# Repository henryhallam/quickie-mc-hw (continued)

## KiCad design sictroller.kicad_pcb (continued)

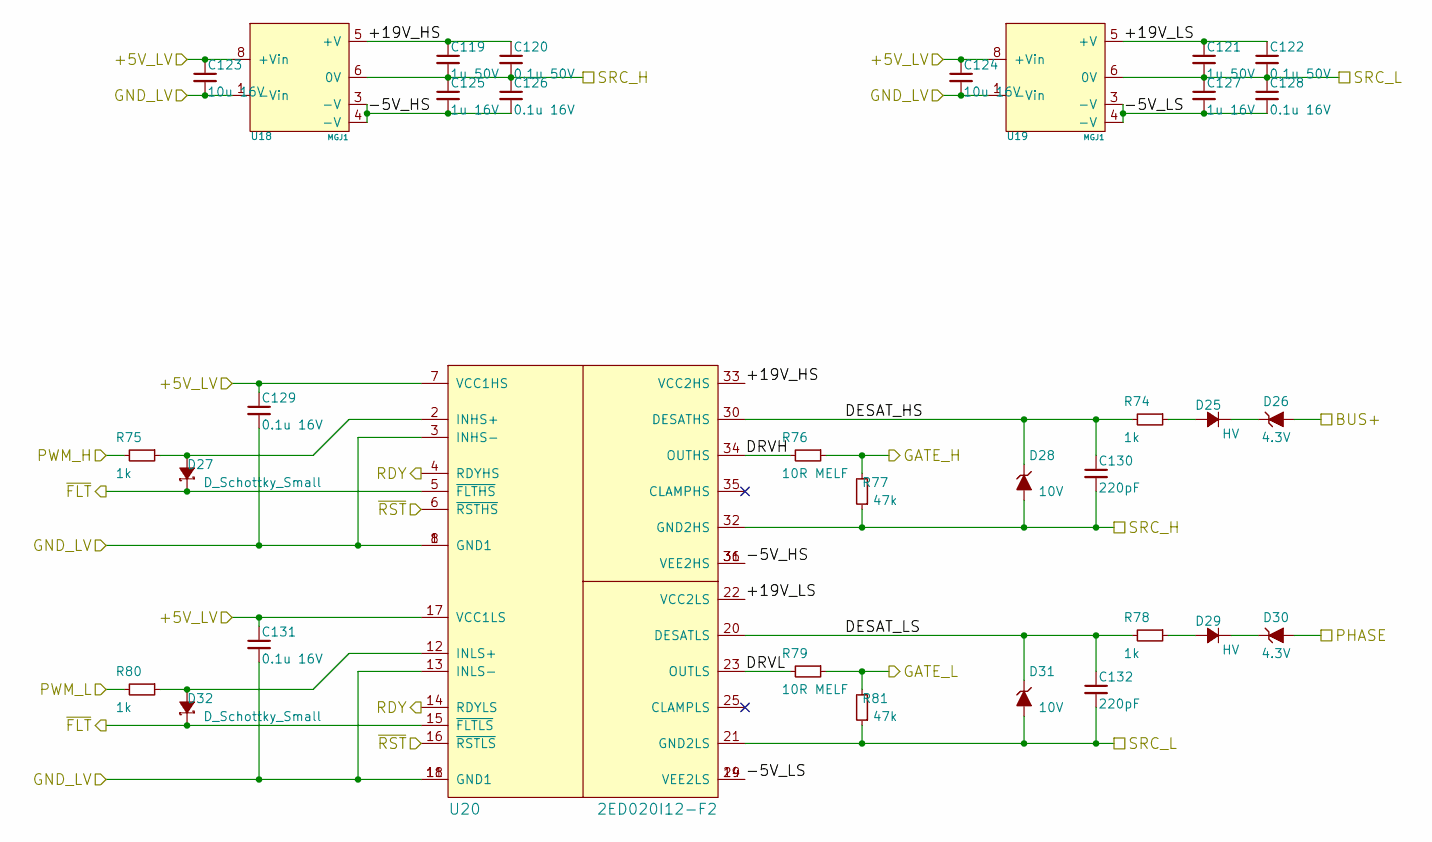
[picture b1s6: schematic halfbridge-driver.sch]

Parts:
C91, C93: 1u 50V; C_0805
C92, C94: 0.1u 50V; C_0603
C95, C96: 10u 16V; C_0805
C97, C99: 1u 16V; C_0603
C98, C100, C101, C103: 0.1u 16V; C_0402
C102, C104: 220pF; C_0402
D9, D13: HV; SMA_Standard
D10, D14: 4.3V; SOD-523
D11, D16: D_Schottky_Small; SOD-523
D12, D15: 10V; SOD-523
R58, R59, R62, R64: 1k; R_0402
R60, R63: 10R MELF; MELF-0204
R61, R65: 47k; R_0805
U12, U13: MGJ1
U14: 2ED020I12-F2; PG-DSO-36-58

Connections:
+5VD: C95.1, C96.1, C101.1, C103.1, U12.8 (+Vin), U13.8 (+Vin), U14.7 (VCC1HS), U14.17 (VCC1LS); also elsewhere on the board
/Power stage/Halfbridge Driver A/+19V_HS: C91.1, C92.1, U12.5 (+V), U14.33 (VCC2HS)
/Power stage/Halfbridge Driver A/+19V_LS: C93.1, C94.1, U13.5 (+V), U14.22 (VCC2LS)
/Power stage/Halfbridge Driver A/-5V_HS: C97.2, C98.2, U12.3 (-V), U12.4 (-V), U14.31 (VEE2HS), U14.36 (VEE2HS)
/Power stage/Halfbridge Driver A/-5V_LS: C99.2, C100.2, U13.3 (-V), U13.4 (-V), U14.19 (VEE2LS), U14.24 (VEE2LS)
/Power stage/Halfbridge Driver A/DESAT_HS: C102.1, D12.1 (K), R58.2, U14.30 (DESATHS)
/Power stage/Halfbridge Driver A/DESAT_LS: C104.1, D15.1 (K), R62.2, U14.20 (DESATLS)
/Power stage/Halfbridge Driver A/DRVH: R60.2, U14.34 (OUTHS)
/Power stage/Halfbridge Driver A/DRVL: R63.2, U14.23 (OUTLS)
/Power stage/Halfbridge Driver A/GATE_H: R60.1, R61.2; also elsewhere on the board
/Power stage/Halfbridge Driver A/GATE_L: R63.1, R65.2; also elsewhere on the board
/Power stage/Halfbridge Driver A/PWM_H: R59.2; also elsewhere on the board
/Power stage/Halfbridge Driver A/PWM_L: R64.2; also elsewhere on the board
/Power stage/Halfbridge Driver A/RDY: U14.4 (RDYHS), U14.14 (RDYLS); also elsewhere on the board
/Power stage/Halfbridge Driver A/SRC_H: C91.2, C92.2, C97.1, C98.1, C102.2, D12.2 (A), R61.1, U12.6 (0V), U14.32 (GND2HS); also elsewhere on the board
/Power stage/Halfbridge Driver A/SRC_L: C93.2, C94.2, C99.1, C100.1, C104.2, D15.2 (A), R65.1, U13.6 (0V), U14.21 (GND2LS); also elsewhere on the board
/Power stage/Halfbridge Driver A/~FLT: D11.1 (K), D16.1 (K), U14.5 (~FLTHS), U14.15 (~FLTLS); also elsewhere on the board
/Power stage/Halfbridge Driver A/~RST: U14.6 (~RSTHS), U14.16 (~RSTLS); also elsewhere on the board
BUS+: D10.2 (A); also elsewhere on the board
GND: C95.2, C96.2, C101.2, C103.2, U12.1 (-Vin), U13.1 (-Vin), U14.1 (GND1), U14.3 (INHS-), U14.8 (GND1), U14.11 (GND1), U14.13 (INLS-), U14.18 (GND1); also elsewhere on the board
unnamed: D9.2 (A), R58.1
unnamed: D9.1 (K), D10.1 (K)
unnamed: D11.2 (A), R59.1, U14.2 (INHS+)
unnamed: D13.1 (K), D14.1 (K)
unnamed: D13.2 (A), R62.1
unnamed: D16.2 (A), R64.1, U14.12 (INLS+)
PHASE_A: D14.2 (A); also elsewhere on the board

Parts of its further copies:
C105, C107, C119, C121: 1u 50V; C_0805
C106, C108, C120, C122: 0.1u 50V; C_0603
C109, C110, C123, C124: 10u 16V; C_0805
C111, C113, C125, C127: 1u 16V; C_0603
C112, C114, C115, C117, C126, C128, C129, C131: 0.1u 16V; C_0402
C116, C118, C130, C132: 220pF; C_0402
D17, D21, D25, D29: HV; SMA_Standard
D18, D22, D26, D30: 4.3V; SOD-523
D19, D24, D27, D32: D_Schottky_Small; SOD-523
D20, D23, D28, D31: 10V; SOD-523
R66, R67, R70, R72, R74, R75, R78, R80: 1k; R_0402
R68, R71, R76, R79: 10R MELF; MELF-0204
R69, R73, R77, R81: 47k; R_0805
U15, U16, U18, U19: MGJ1
U17, U20: 2ED020I12-F2; PG-DSO-36-58

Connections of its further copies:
+5VD: C109.1, C110.1, C115.1, C117.1, C123.1, C124.1, C129.1, C131.1, U15.8 (+Vin), U16.8 (+Vin), U17.7 (VCC1HS), U17.17 (VCC1LS), U18.8 (+Vin), U19.8 (+Vin), U20.7 (VCC1HS), U20.17 (VCC1LS); also elsewhere on the board
/Power stage/Halfbridge Driver A/RDY: U17.4 (RDYHS), U17.14 (RDYLS), U20.4 (RDYHS), U20.14 (RDYLS); also elsewhere on the board
/Power stage/Halfbridge Driver A/~FLT: D19.1 (K), D24.1 (K), D27.1 (K), D32.1 (K), U17.5 (~FLTHS), U17.15 (~FLTLS), U20.5 (~FLTHS), U20.15 (~FLTLS); also elsewhere on the board
/Power stage/Halfbridge Driver A/~RST: U17.6 (~RSTHS), U17.16 (~RSTLS), U20.6 (~RSTHS), U20.16 (~RSTLS); also elsewhere on the board
/Power stage/Halfbridge Driver B/+19V_HS: C105.1, C106.1, U15.5 (+V), U17.33 (VCC2HS)
/Power stage/Halfbridge Driver B/+19V_LS: C107.1, C108.1, U16.5 (+V), U17.22 (VCC2LS)
/Power stage/Halfbridge Driver B/-5V_HS: C111.2, C112.2, U15.3 (-V), U15.4 (-V), U17.31 (VEE2HS), U17.36 (VEE2HS)
/Power stage/Halfbridge Driver B/-5V_LS: C113.2, C114.2, U16.3 (-V), U16.4 (-V), U17.19 (VEE2LS), U17.24 (VEE2LS)
/Power stage/Halfbridge Driver B/DESAT_HS: C116.1, D20.1 (K), R66.2, U17.30 (DESATHS)
/Power stage/Halfbridge Driver B/DESAT_LS: C118.1, D23.1 (K), R70.2, U17.20 (DESATLS)
/Power stage/Halfbridge Driver B/DRVH: R68.2, U17.34 (OUTHS)
/Power stage/Halfbridge Driver B/DRVL: R71.2, U17.23 (OUTLS)
/Power stage/Halfbridge Driver B/GATE_H: R68.1, R69.2; also elsewhere on the board
/Power stage/Halfbridge Driver B/GATE_L: R71.1, R73.2; also elsewhere on the board
/Power stage/Halfbridge Driver B/PWM_H: R67.2; also elsewhere on the board
/Power stage/Halfbridge Driver B/PWM_L: R72.2; also elsewhere on the board
/Power stage/Halfbridge Driver B/SRC_H: C105.2, C106.2, C111.1, C112.1, C116.2, D20.2 (A), R69.1, U15.6 (0V), U17.32 (GND2HS); also elsewhere on the board
/Power stage/Halfbridge Driver B/SRC_L: C107.2, C108.2, C113.1, C114.1, C118.2, D23.2 (A), R73.1, U16.6 (0V), U17.21 (GND2LS); also elsewhere on the board
/Power stage/Halfbridge Driver C/+19V_HS: C119.1, C120.1, U18.5 (+V), U20.33 (VCC2HS)
/Power stage/Halfbridge Driver C/+19V_LS: C121.1, C122.1, U19.5 (+V), U20.22 (VCC2LS)
/Power stage/Halfbridge Driver C/-5V_HS: C125.2, C126.2, U18.3 (-V), U18.4 (-V), U20.31 (VEE2HS), U20.36 (VEE2HS)
/Power stage/Halfbridge Driver C/-5V_LS: C127.2, C128.2, U19.3 (-V), U19.4 (-V), U20.19 (VEE2LS), U20.24 (VEE2LS)
/Power stage/Halfbridge Driver C/DESAT_HS: C130.1, D28.1 (K), R74.2, U20.30 (DESATHS)
/Power stage/Halfbridge Driver C/DESAT_LS: C132.1, D31.1 (K), R78.2, U20.20 (DESATLS)
/Power stage/Halfbridge Driver C/DRVH: R76.2, U20.34 (OUTHS)
/Power stage/Halfbridge Driver C/DRVL: R79.2, U20.23 (OUTLS)
/Power stage/Halfbridge Driver C/GATE_H: R76.1, R77.2; also elsewhere on the board
/Power stage/Halfbridge Driver C/GATE_L: R79.1, R81.2; also elsewhere on the board
/Power stage/Halfbridge Driver C/PWM_H: R75.2; also elsewhere on the board
/Power stage/Halfbridge Driver C/PWM_L: R80.2; also elsewhere on the board
/Power stage/Halfbridge Driver C/SRC_H: C119.2, C120.2, C125.1, C126.1, C130.2, D28.2 (A), R77.1, U18.6 (0V), U20.32 (GND2HS); also elsewhere on the board
/Power stage/Halfbridge Driver C/SRC_L: C121.2, C122.2, C127.1, C128.1, C132.2, D31.2 (A), R81.1, U19.6 (0V), U20.21 (GND2LS); also elsewhere on the board
BUS+: D18.2 (A), D26.2 (A); also elsewhere on the board
GND: C109.2, C110.2, C115.2, C117.2, C123.2, C124.2, C129.2, C131.2, U15.1 (-Vin), U16.1 (-Vin), U17.1 (GND1), U17.3 (INHS-), U17.8 (GND1), U17.11 (GND1), U17.13 (INLS-), U17.18 (GND1), U18.1 (-Vin), U19.1 (-Vin), U20.1 (GND1), U20.3 (INHS-), U20.8 (GND1), U20.11 (GND1), U20.13 (INLS-), U20.18 (GND1); also elsewhere on the board
unnamed: D17.1 (K), D18.1 (K)
unnamed: D17.2 (A), R66.1
unnamed: D19.2 (A), R67.1, U17.2 (INHS+)
unnamed: D21.1 (K), D22.1 (K)
unnamed: D21.2 (A), R70.1
unnamed: D24.2 (A), R72.1, U17.12 (INLS+)
unnamed: D25.1 (K), D26.1 (K)
unnamed: D25.2 (A), R74.1
unnamed: D27.2 (A), R75.1, U20.2 (INHS+)
unnamed: D29.1 (K), D30.1 (K)
unnamed: D29.2 (A), R78.1
unnamed: D32.2 (A), R80.1, U20.12 (INLS+)
PHASE_B: D22.2 (A); also elsewhere on the board
PHASE_C: D30.2 (A); also elsewhere on the board

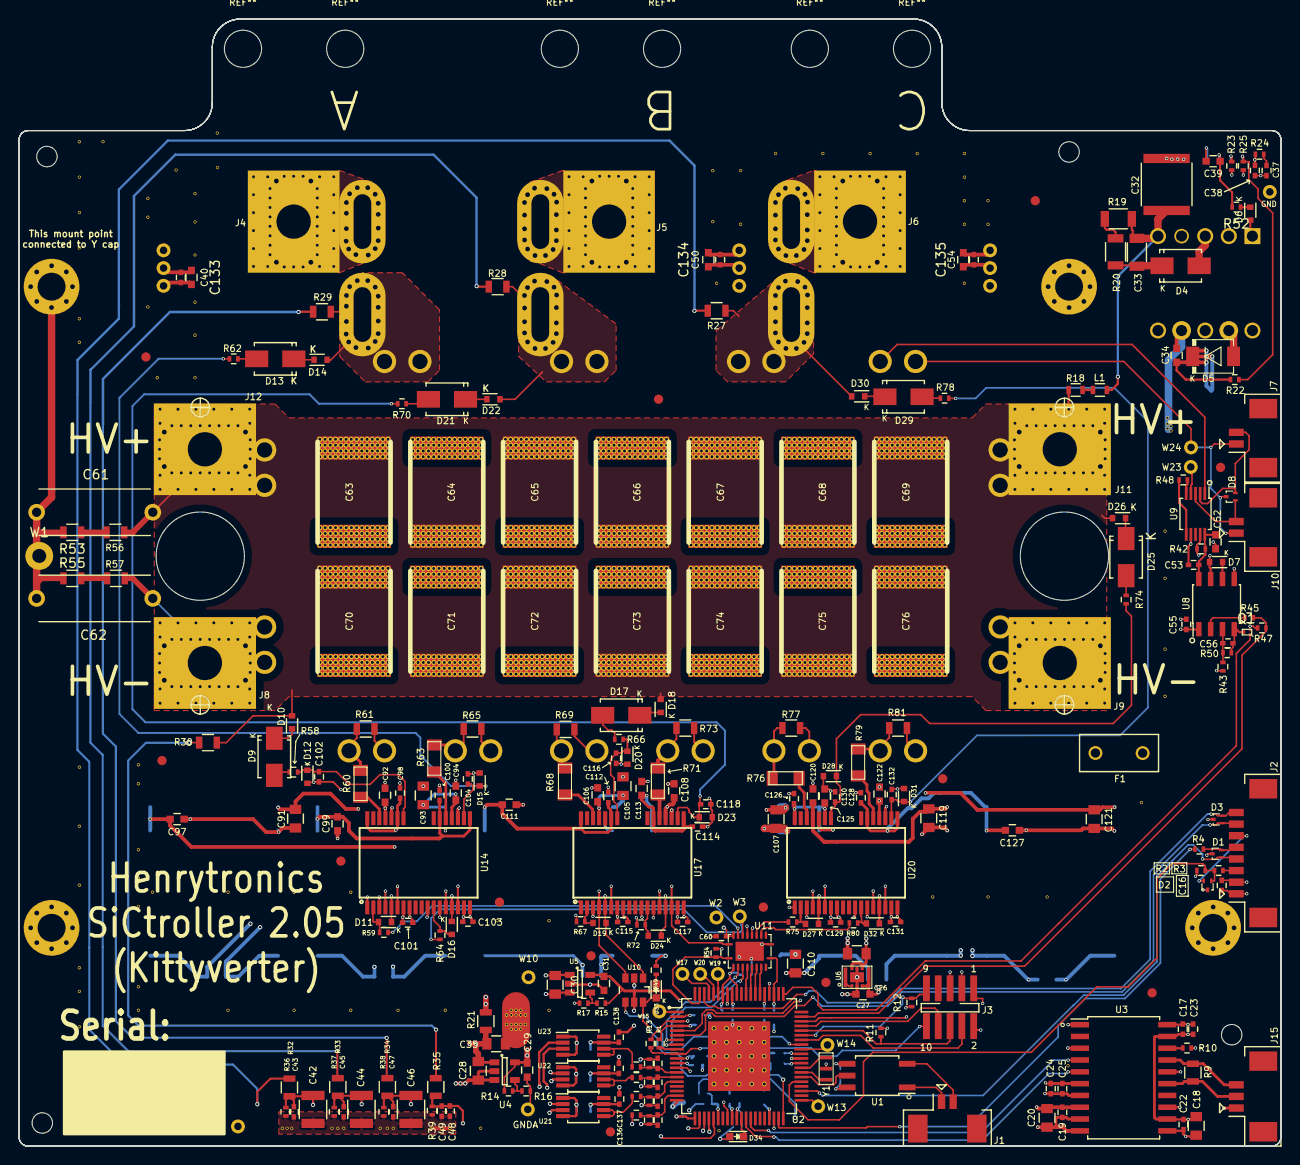
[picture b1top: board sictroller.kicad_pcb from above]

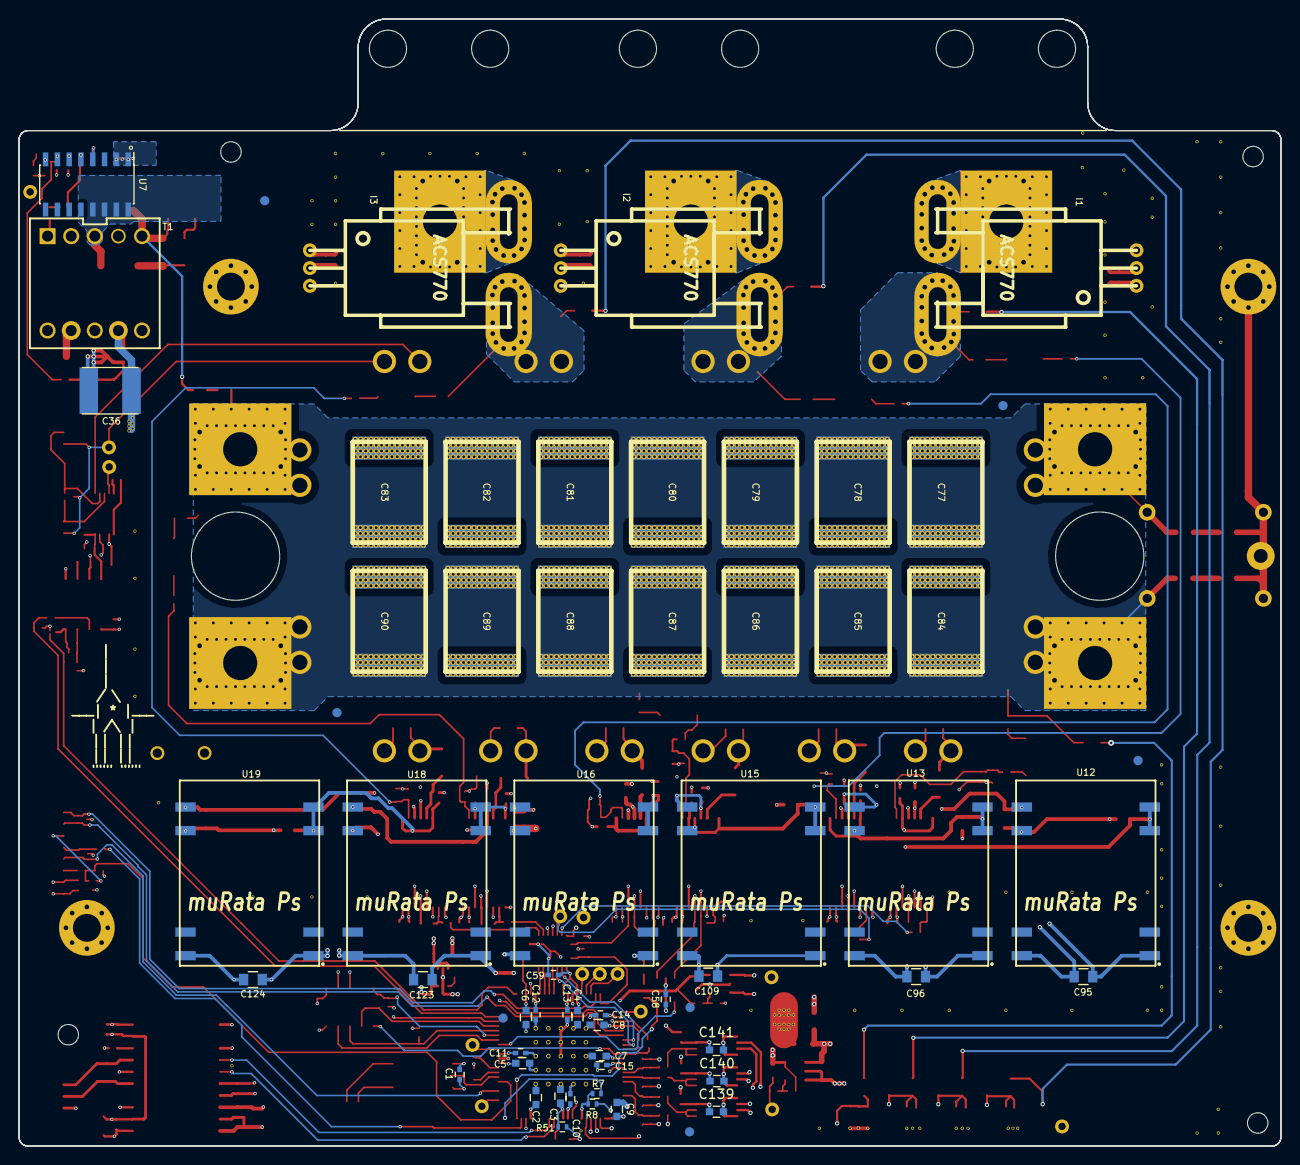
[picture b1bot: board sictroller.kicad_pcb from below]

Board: 6 copper layers, 135.8 x 121.3 mm, 351 parts (61 on the bottom side), 176 nets.

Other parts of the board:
GNDVIA: VIA
GNDVIA#2, GNDVIA#3, GNDVIA#4, GNDVIA#5, GNDVIA#6: VIA
MNT**: MountingHole_2.2mm_M2_DIN965
MNT**#2, MNT**#3, MNT**#4: MountingHole_2.2mm_M2_DIN965

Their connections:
GND: GNDVIA.1, GNDVIA#2.1, GNDVIA#3.1, GNDVIA#4.1, GNDVIA#5.1, GNDVIA#6.1; also elsewhere on the board

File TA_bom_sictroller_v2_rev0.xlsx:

Reference Designator | Quantity | Description/Value | Manufacturer Part Number (MPN)
C13,C10,C11,C12,C14,C15 | 6 | CAP CER 2.2uF 6.3V | GRM155C70J225KE11D
C131,C129,C128,C126,C117,C115,C114,C112,C103,C101,C100,C98,C48,C1,C24,C22,C21,C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 | 29 | CAP CER 0.1uF 16V | GCM155R71C104KA55J
C132,C130,C118,C116,C104,C102 | 6 | DNA | DNA
C25,C23 | 2 | CAP CER 0.01uF 50V | GCM155R71H103KA55D
C37 | 1 | CAP CER 0.047uF 25V | GCM155R71E473KA55D
C38,C57,C51,C41 | 4 | CAP CER 2200pF 50V | GCM155R71H222KA37D
C49,C47,C45,C43 | 4 | CAP CER 470pF 100V | GCM155R72A471KA37D
C122,C120,C108,C106,C94,C92 | 6 | CAP CER 0.1uF 50V | GCJ188R71H104KA12D
C127,C125,C113,C111,C99,C97,C34,C39,C52 | 9 | CAP CER 1uF 35V | CGA3E1X7R1V105K080AE
C31,C29,C27 | 3 | CAP CER 10uF 10V | GRT188C81A106ME13D
C9,C8,C7,C6,C5,C4,C3,C2 | 8 | CAP CER 2.2uF 10V | C1608X7R1A225K080AE
C121,C119,C107,C105,C93,C91 | 6 | CAP CER 1uF 50V | GCJ21BR71H105KA01L
C124,C123,C110,C109,C96,C95,C20,C18,C30,C28,C26,C35 | 12 | CAP CER 10uF 16V | CGA4J1X7S1C106M125AE
C33 | 1 | CAP CER 470pF 1KV | GRM31B7U3A471JW31L
C46,C44,C42 | 3 | CAP PPS 0.1uF 16V | ECH-U1C104GX5
C62,C61 | 2 | CAP CER 0.047UF 1KV | C1210W473KDRACTU
C32 | 1 | CAP CER 0.47UF 1KV | 2220Y1K00474KXTWS2
C36 | 1 | CAP CER 100UF 16V | CKG57NX7S1C107M500JJ
C90,C89,C88,C87,C86,C85,C84,C83,C82,C81,C80,C79,C78,C77,C76,C75,C74,C73,C72,C71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 | 28 | CAP CER 1uF 500V | B58031I5105M
D29,D25,D21,D17,D13,D9 | 6 | DIODE 1kV ULTRAFAST | US1M
D3,D2,D1 | 3 | TVS 3.3V DUAL | ESD7C3.3DT5G
D30,D26,D22,D18,D14,D10 | 6 | DIODE ZENER 4.3V | BZT585B4V3T
D31,D28,D23,D20,D15,D12 | 6 | DIODE ZENER 10V | BZT585B10T
D32,D27,D24,D19,D16,D11,D7 | 7 | DIODE SCHOTTKY SMALL SIGNAL | RB521S30T1G
D33 | 1 | LED RED | XZM2ACR53W-1
D34 | 1 | LED YELLOW | XZM2ACY53W-1
D4 | 1 | DIODE 1kV FAST | RS1M
D5 | 1 | DIODE SCHOTTKY 5A | PMEG3050EP
D6 | 1 | DIODE FAST SW | 1N4148WT-7
D8 | 1 | TVS 5V DUAL | ESD7C5.0DT5G
F1 | 1 | FUSE 0.75A | BK/PCC-3/4-R
FID1,FID2,FID3,FID4,FID5,FID6,FID7,FID8,FID9,FID10,FID11,FID12,FID13,FID14,FID1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 | 20 | Fiducials | DNA
GNDVIA,GNDVIA,GNDVIA,GNDVIA,GNDVIA,REF**,REF**,GNDVIA | 8 | Stitching vias | DNA
I3,I2,I1 | 3 | SENS HALL-EFF 100A | ACS770LCB-100B-PFF-T
J10,J7,J1 | 3 | CONN PICOBLADE 2 | 53261-0271
J12,J11,J9,J8,J6,J5,J4 | 7 | WIRE LUG PCB IHI | B6A-PCB
J14 | 1 | CONN PICOBLADE 5 | 53261-0571
J15 | 1 | CONN PICOBLADE 3 | 53261-0371
J2 | 1 | CONN PICOBLADE 8 | 53261-0871
J3 | 1 | CONN 2x5 1.27mm | FTSH-105-01-L-DV-K
L1 | 1 | IND 10uH 380mA | CBMF1608T100K
MNT1,MNT2,MNT3,MNT4 | 4 | Mounting holes | DNA
Q1 | 1 | MOSFET N-CH 30V | CSD17483F4
Q2 | 1 | Power module | DNA
R60,R79,R76,R71,R68,R63 | 6 | RES 10R 2% 0.4W | CMA02040X1009GB300
R13,R12,R11,R1 | 4 | RES 4.7K 1% | ERJ-2RKF4701X
R44,R40,R26 | 3 | RES 1.8K 0.1% | ERA-2AEB182X
R47,R50 | 2 | RES 100K 1% | ERJ-2RKF1003X
R54,R10,R8,R7,R43,R42 | 6 | RES 10K 1% | ERJ-2RKF1002X
R5 | 1 | RES 169R 0.1% | ERA-2AEB1690X
R22,R3 | 2 | RES 16.9K 0.1% | ERA-2AEB1692X
R80,R78,R75,R74,R72,R70,R67,R66,R64,R62,R59,R58 | 12 | RES 1K 1% | ERJ-2RKF1001X
R48 | 1 | RES 2.7K 0.1% | ERA-2AEB272X
R15,R14 | 2 | RES 42.2K 0.1% | ERA-2AEB4222X
R46,R41,R31,R24 | 4 | RES 3.3K 0.1% | ERA-2AEB332X
R39,R38,R37,R36 | 4 | RES 3.6K 0.1% | ERA-2AEB362X
R6,R4,R49,R51 | 4 | RES 330R 0.1% | ERA-2AEB331X
R25,R2 | 2 | RES 33K 0.1% | ERA-2AEB333X
R45 | 1 | RES 56K 1% | ERJ-2RKF5602X
R17,R16 | 2 | RES 10.7K 0.1% | ERA-2AEB1072X
R23 | 1 | DNA | DNA
R18 | 1 | RES 22R 1% | ERJ-PA3F22R0V
R21 | 1 | FERRITE BEAD | BK2125HS102-T
R35,R34,R33,R32,R30,R29,R28,R27 | 8 | RES 300K 1% HV | ERJ-P06F3003V
R57,R56 | 2 | RES 1M 5% HV | ERJ-P06J105V
R61,R65,R69,R73,R77,R81 | 6 | RES 47K 5% | ERJ-6GEYJ473V
R9 | 1 | RES 120R 5% | ERJ-P06J121V
R20,R19 | 2 | RES 51K 5% HV | ERJ-P08J513V
REF**,REF**,REF**,REF**,REF**,REF** | 6 | Mounting holes | DNA
T1 | 1 | Transformer flyback | 7508110151
TH1,TH2 | 2 | Thermistor | NCP15XW153J03RC
TIE1 | 1 | Net tie | DNA
U1 | 1 | Optocoupler logic | ACPL-M61L
U10 | 1 | Dual inverter | 74LVC2G04GV
U11 | 1 | Level shifter 8-bit | TXS0108ERGYR
U19,U18,U16,U15,U13,U12 | 6 | Iso DC-DC | MGJ1D051905MPC
U2 | 1 | MCU DSP Piccolo Instaspin | TMS320F28069MPFPQ
U20,U17,U14 | 3 | Iso half bridge gate drive | 2ED020I12-F2
U3 | 1 | XCVR CAN ISO | ADM3053BRWZ
U5,U4 | 2 | REG LDO ADJ | TPS76201DBV
U6 | 1 | DC-DC micro step-down | XCL221B181ER
U7 | 1 | AC/DC converter 800V | VIPER26HD
U8 | 1 | Dual isolator | ADUM5241
U9 | 1 | 4ch thermistor interface | MAX6691
W3,W2,W20,W19,W17,W15,W14,W13,W12,W11,W10,W9,W5,W1,W23,W24,W4 | 17 | Test points | DNA
Y1 | 1 | RESONATOR 20 MHz | CSTCE20M0V13

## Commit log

2016-08-03 Initial commit - symbols for ControlCard and level shifter
2016-08-03 Hierarchical schematic
2016-08-05 V0 schematic complete (?)
2016-08-06 Annotate, fix schematic DRC, footprint for DIMM100
2016-08-07 Footprints assigned, netlist generated - ready for layout
2016-08-07 More aux pins, SKUs for some components
2016-08-07 Footprint for barrel jack PJ-102B
2016-08-07 PCB outline, mounting holes and J12/X1 placement (approx) to match CGD15FB45P1
2016-08-07 Add test points; PCB connectors placed
2016-08-07 Change J6 (microfit) pinning for better routing of HV
2016-08-07 Most parts placed-ish
2016-08-07 Swap level shifter pins for easier routing
2016-08-07 About to start routing
2016-08-07 Started routing
2016-08-08 routing, but weird netnames on PWM
2016-08-08 Fix top-level PWM miswiring
2016-08-08 PWM and faults routed
2016-08-08 Routing progress
2016-08-08 Further routing progress
2016-08-08 routing routing
2016-08-08 Layout complete
2016-09-15 V1.0 fab output
2016-09-15 errata from V1.0 bringup
2016-09-15 Footprint for CCS050M12CM2
2016-09-15 Rename schematic sheets for V2
2016-09-15 Add CCS050M12CM2 schematic symbol to sictroller.lib
2016-09-15 Add symbol for 2ED020I12-F2 dual iso gate driver
2016-09-15 PG-DSO-36-58 footprint for 2ED020I12-F2
2016-09-15 MGJ1 iso gdrv psu symbol + footprint
2016-09-21 ACS770
2016-09-25 Footprint for Ceralink L-style
2016-10-03 schematic updates for V2; PCB draft layout
2016-10-05 progress on V2 schematic
2016-10-06 more v2 progress
2016-10-06 further V2 progress
2016-10-07 V2 schem complete, footprints not assigned
2016-10-07 Add TVS protection to signal I/O. Reannotate. Assign some footprints.
2016-10-07 footprints assigned for instaspin and LV power
2016-10-07 Footprints assigned for all except halfbridge-driver
2016-10-07 Footprint assignment complete
2016-10-07 Placed SiC module, DC link caps, HV / phase terminals
2016-10-07 Fix missing/duped pin assignments for 2ED020I12-F2 low-side output
2016-10-07 Place central 4 MGJ1s
2016-10-07 New, more boring placement of MGJ1s (vias would have been difficult)
2016-10-07 Placement progress
2016-10-07 Power stage / gate drive approx placement complete
2016-10-07 started placement of HV-LV stepdown
2016-10-08 some area thing?
2016-10-08 stepdown PSU placed
2016-10-08 Add more ceralinks on rear
2016-10-09 Add 1568 vias in DC link cap pads
2016-10-11 Improved footprint for B6A-PCB
2016-10-11 phase connection tweaks
2016-10-11 Zones for phase connections
2016-10-11 Zones for phase connections 2
2016-10-11 Zones for phase connections 3
2016-10-11 Swap PWM nets on 28069M for easier routing
2016-10-11 Add aux connector for vibe monitor
2016-10-12 some logic placement progress
2016-10-13 Placement almost complete
2016-10-13 Initial placement ~complete
2016-10-17 Placed AGND plane
2016-10-18 Remove underside solder mask openings from PFP package
2016-10-18 routed underside of 28069M
2016-10-18 Route CAN isolated section
2016-10-18 most planes in place
2016-10-18 gate drive source planes in place
2016-10-19 routing progress - gate driver LV sides complete
2016-10-19 3.3V and 1.8V supplies routed; fixed wrong connections on 1.8V regulator
2016-10-20 routing routing routing
2016-10-20 further routing; add fault LED
2016-10-20 getting there..
2016-10-20 the end is in sight
2016-10-21 0 not connected
2016-10-21 DRC pass (haven't checked 9/9 on inner layers)
2016-10-21 inner layer 9/9 visually checked; starting silkscreen
2016-10-21 silkscreen progress
2016-10-21 silkscreen complete top side?
2016-10-21 Silkscreen done both sides, added aux LED
2016-10-21 further trivial tweaks
2016-10-21 Add fiducials
2016-10-21 Add M2 mounting holes for cover
2016-10-21 As sent to Tempo 2016-10-21
2016-10-24 fab notes
2016-10-28 Minor fixups from Tempo DFM
2016-12-03 Errata from v2.0 bringup
2016-12-03 V2.1: Fixes for V2.0 bugs
2016-12-03 Add trivial readme
2017-03-16 CURRENT: Add diff amps, bypass caps
    Other file changes appear to be result of annotation
2017-03-17 YCAPS: Add real safety caps, dual Res
2017-03-17 WIP: Moving around planes
2017-03-17 WIP: Closing in, better planes and long trace
2017-03-17 JTAG/BOOT: Pulldown TRST for boot from Flash
2017-03-18 AUXADC: Remove connector
2017-03-18 WIP: Closer, mostly passing DRC
2017-03-18 WIP: Vsense remaining
2017-03-19 TESTPOINT: Remove some
2017-03-19 WIP: Passes DRC. Need to remove fuse and merge gnd
2017-03-20 Checking: Hopefully complete for production
2017-12-25 errata updates and schematic comments
2018-05-13 Kicad rescue
